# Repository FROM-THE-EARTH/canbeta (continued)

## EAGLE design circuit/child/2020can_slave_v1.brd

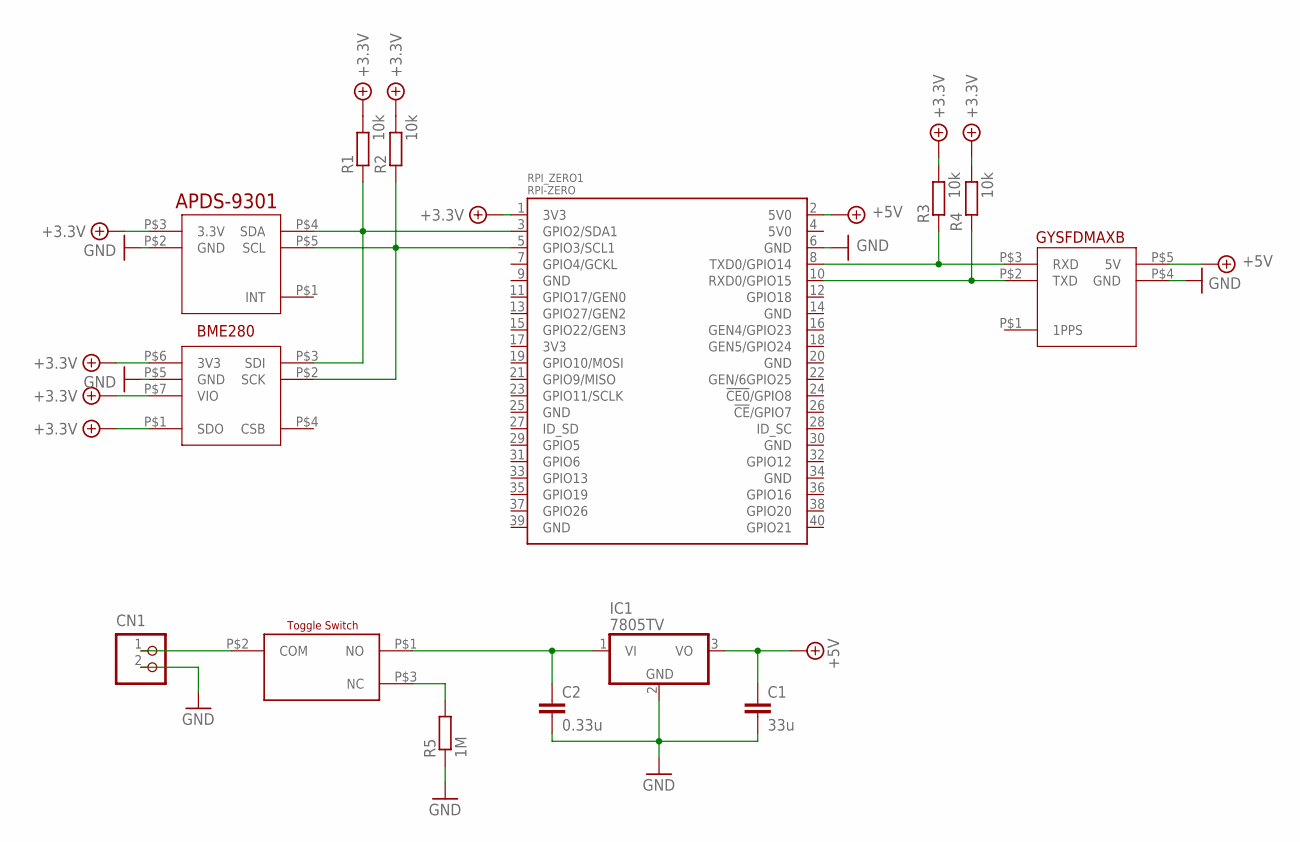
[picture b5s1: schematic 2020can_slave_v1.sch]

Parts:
APDS-9301_V1: APDS-9301_V
BME280-1_V1: BME280-1_V
C1: 33u; C5B3
C2: 0.33u; C5B3
CN1: B2P-VH
GYSFDMAXB_V1: GYSFDMAXB_V
IC1: 7805TV; TO220V
R1, R2, R3, R4: 10k; 0207/10
R5: 1M; 0207/10
RPI_ZERO1: RPI-ZERO; RASP_PI_ZERO_BOARD_FULL
SWITCH_2MS1T2B4M2QES1: SWITCH_2MS1T2B4M2QES

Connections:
+4.1V: APDS-9301_V1.P$3 (3.3V), BME280-1_V1.P$6 (3V3), BME280-1_V1.P$7 (VIO), R1.2, R2.2, R3.2, R4.2, RPI_ZERO1.1 (3V3)
+5V: C1.1, GYSFDMAXB_V1.P$5 (5V), IC1.3 (VO), RPI_ZERO1.2 (5V0)
GND: APDS-9301_V1.P$2 (GND), BME280-1_V1.P$5 (GND), C1.2, C2.2, CN1.2, GYSFDMAXB_V1.P$4 (GND), IC1.2 (GND), R5.1, RPI_ZERO1.6 (GND)
unnamed: APDS-9301_V1.P$4 (SDA), BME280-1_V1.P$3 (SDI), R1.1, RPI_ZERO1.3 (GPIO2/SDA1)
unnamed: APDS-9301_V1.P$5 (SCL), BME280-1_V1.P$2 (SCK), R2.1, RPI_ZERO1.5 (GPIO3/SCL1)
unnamed: R5.2, SWITCH_2MS1T2B4M2QES1.P$3 (NC)
unnamed: GYSFDMAXB_V1.P$3 (RXD), R3.1, RPI_ZERO1.8 (TXD0/GPIO14)
unnamed: GYSFDMAXB_V1.P$2 (TXD), R4.1, RPI_ZERO1.10 (RXD0/GPIO15)
V+: CN1.1, SWITCH_2MS1T2B4M2QES1.P$2 (COM)
VIN: C2.1, IC1.1 (VI), SWITCH_2MS1T2B4M2QES1.P$1 (NO)

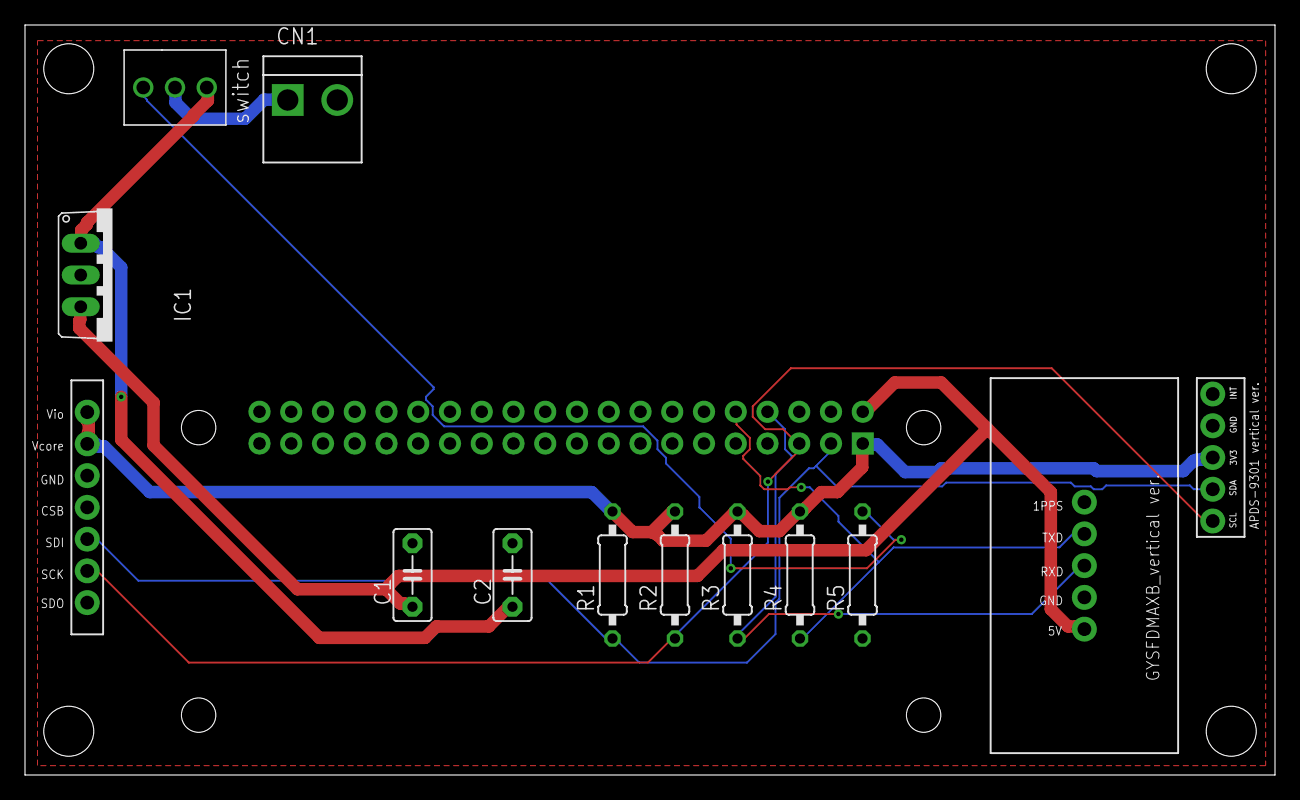
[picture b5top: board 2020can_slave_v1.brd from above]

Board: 2 copper layers, 100.0 x 60.0 mm, 14 parts (1 on the bottom side), 10 nets.

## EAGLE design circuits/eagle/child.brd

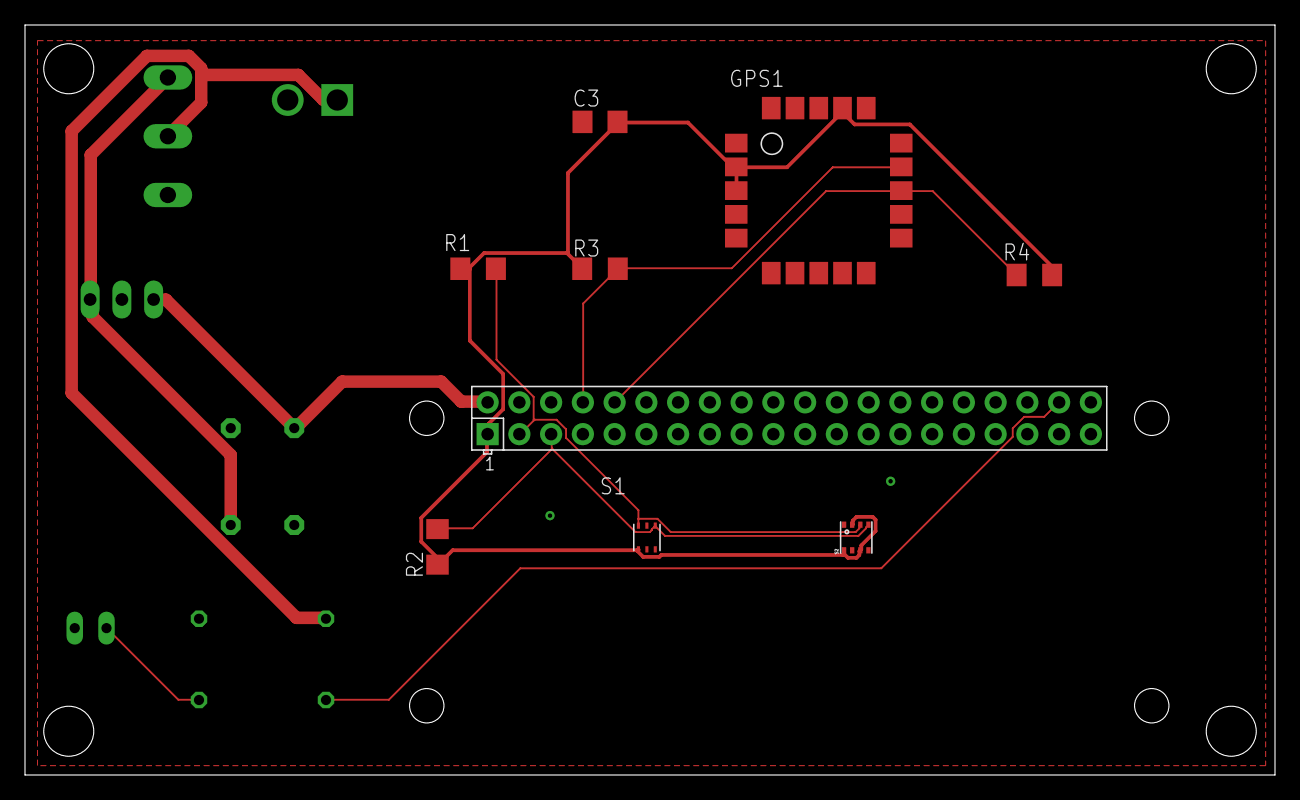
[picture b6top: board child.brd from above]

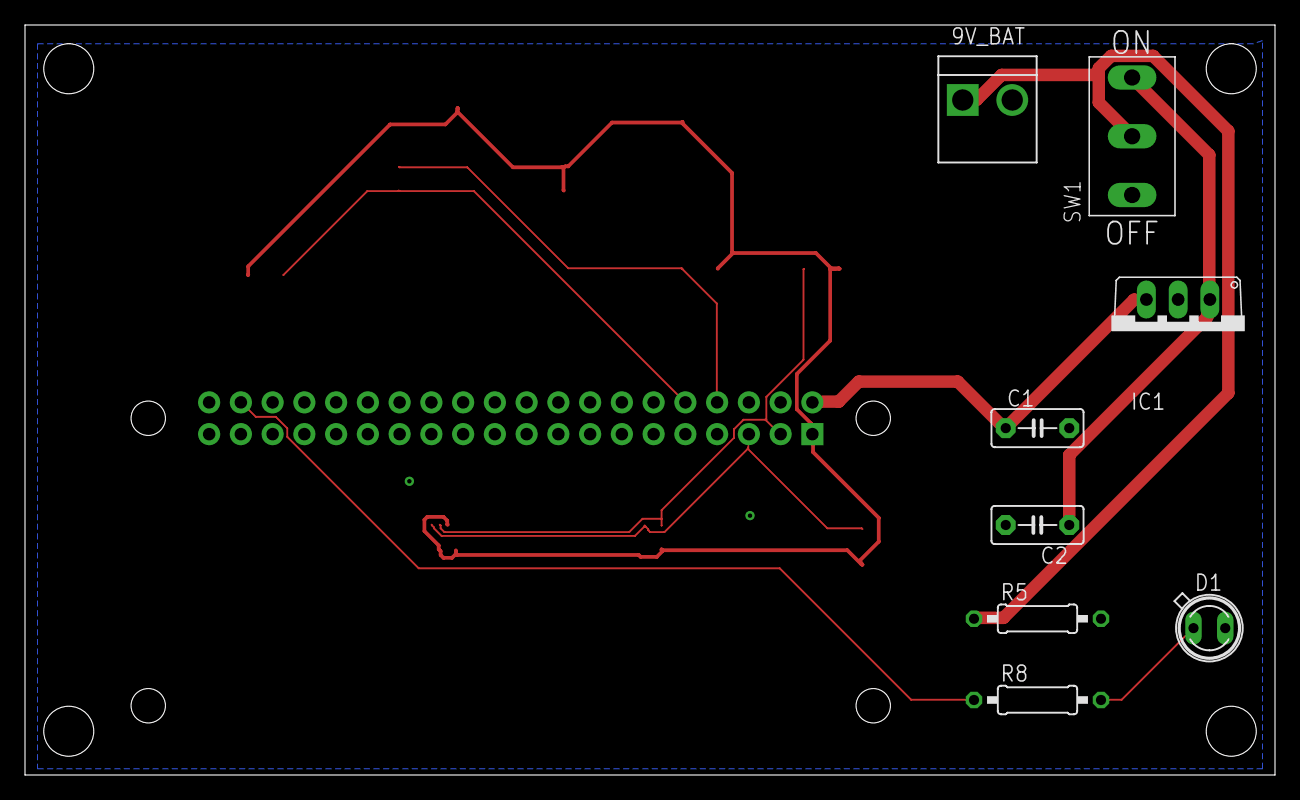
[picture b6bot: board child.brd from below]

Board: 2 copper layers, 100.0 x 60.0 mm, 17 parts (8 on the bottom side), 11 nets.

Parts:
9V_BAT: B2P-VH
C1: 33u; C5B3
C2: 0.33u; C5B3
C3: 0.1u; C1206
D1: SFH482
GPS1: SAM-M8Q
IC1: 7805TV; TO220V
R1, R2, R3, R4: 10k; R1206
R5: 1M; 0207/10
R8: 470; 0207/10
RPI_ZERO1: RPI-ZERO; RASP_PI_ZERO_BOARD_FULL
S1: OPT3002
S2: BME280
SW1: TOGGLE; TOGGLE_1MS1-T1-B1-M2-Q-N-S

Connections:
+3V3: C3.2, GPS1.P$2, GPS1.P$3, GPS1.P$17, R1.2, R2.2, R3.1, R4.1, RPI_ZERO1.1, S1.P$1, S2.P$2, S2.P$6, S2.P$8
+5V: C1.1, IC1.3, RPI_ZERO1.2
GND: 9V_BAT.2, C1.2, C2.2, C3.1, D1.K, GPS1.P$1, GPS1.P$4, GPS1.P$5, GPS1.P$6, GPS1.P$10, GPS1.P$11, GPS1.P$15, GPS1.P$16, GPS1.P$20, IC1.2, R5.2, RPI_ZERO1.9, S1.P$2, S1.P$3, S2.P$1, S2.P$5, S2.P$7
GPS_RXD: GPS1.P$14, R3.2, RPI_ZERO1.8
GPS_TXD: GPS1.P$13, R4.2, RPI_ZERO1.10
unnamed: R8.1, RPI_ZERO1.38
unnamed: D1.A, R8.2
SCL: R2.1, RPI_ZERO1.5, S1.P$4, S2.P$4
SDA: R1.1, RPI_ZERO1.3, S1.P$6, S2.P$3
V+: 9V_BAT.1, R5.1, SW1.P$2
VIN: C2.1, IC1.1, SW1.P$3

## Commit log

2020-08-26 add gitignore
2020-08-26 created node templates
2020-08-26 created main script
2020-08-26 update dependancy for dev-env
2020-08-26 Update LICENSE
2020-08-26 formatted code
2020-08-26 add empty test flies
2020-08-27 modified package to reflect change of pisat
2020-08-28 update to reflect changes of pisat
2020-08-28 add pigpio
2020-08-29 add analysis of the result of Precursor
2020-08-29 add packages for dev
2020-08-29 fix typo
2020-08-29 add legend and fix the unit of gyro
2020-09-10 add hogehoge
2020-09-28 added HogeHoge
2020-09-28 added another hogehoge
2020-09-28 fallin'
2020-09-28 fallin''
2020-09-28 add deque
2020-09-30 add docs to share information about development
2020-09-30 create a script for adding the can09 package into site-packages
2020-09-30 add docs about hardware and testing
2020-10-03 fixed
2020-10-03 added some constants
2020-10-03 add ave calc
2020-10-03 fix misspelled
2020-10-03 fix dependancy of pisat
2020-10-03 add .venv
2020-10-03 add nodes dir in docs
2020-10-04 added some const
2020-10-19 set fethandler in main and para
2020-10-22 add datasheets of devices to be used
2020-10-22 add circuit's data
2020-10-23 add files for flowcharts
2020-10-23 add empty test scripts
2020-10-23 added the flow charts
2020-10-23 added flowchart
2020-10-24 observe gap of acc_x
2020-10-24 add server package for handling wireless commands
2020-10-24 add dir for experiments
2020-10-24 remove SC SIGNAL from the format
2020-10-24 separated RequestParams from Request
2020-10-25 fixed import error and added RequestCommand to represent an exception about command
2020-10-25 added docs for server
2020-10-27 retake
2020-10-27 para&fallin flowchart
2020-10-27 rework falling_node
2020-10-27 update hardware settings
2020-10-29 E2E exp for first phase
2020-10-29 exp_falling
2020-10-29 rm miss files
2020-11-05 removed useless file
2020-11-05 put together flowcharts into a single file
2020-11-05 modified all flowcharts
2020-11-05 added a dir for e2e test
2020-11-05 updated the falling experiment
2020-11-07 added util file
2020-11-10 updated some constants
2020-11-10 deleted some lines
2020-11-10 updated i controller n deleted reset() method
2020-11-12 added sample-timer
2020-11-12 added sample conter
2020-11-13 copied first_running_node.py
2020-11-13 added TODO
2020-11-13 modified some constants
2020-11-14 update because of the update of pisate
2020-11-14 changed setting because of the change of pisat
2020-11-14 add new nodes
2020-11-14 add new dir named image
2020-11-14 update gitignore
2020-11-15 changed accordin to the change in PIDController.py
2020-11-15 added options
2020-11-15 changed ACCEPTABLE_MOE to SSE_RATIO
2020-11-15 added limit_sensitivity_method.py
2020-11-17 wrote without using manager
2020-11-19 Created new directory for the control station
2020-11-19 Added a script for checking current altitude on terminal
2020-11-19 Fixed because of the update of pisat
2020-11-19 Removed and fixed some points where bugs may exist
2020-11-19 update method of falling experiment
2020-11-19 change so that FallingModel can emit relative altitude
2020-11-19 Added new test for tegus
2020-11-19 Fixed typo
2020-11-19 remove im920
2020-11-19 Added results of experiment
2020-11-19 Removed some dependencies because installation troubles occured.
2020-11-19 Added document about trouble shooting
2020-11-20 Updated trouble-shooting about IM920
2020-11-20 Updated trouble-shooting about serial communication
2020-11-20 Added device IDs of IM920
2020-11-20 Fixed typos
2020-11-20 Implemented MissionStandbyNode
2020-11-20 Updated each settings
2020-11-20 Fixed so that any encodings can be used
2020-11-20 Added SocketTransceiver as a component
2020-11-20 Updated scripts for control station
2020-11-20 Removed dev-packages
2020-11-20 Changed baudrate of IM920 and GPS
2020-11-20 Configured main.py of child
2020-11-20 Moved setting of altitude on the ground
2020-11-20 Changed start Node as MissionStandbyNode
2020-11-20 Built MissionStandbyNode.
2020-11-20 Built ChildServerNode.
2020-11-20 Added the attribute of length of request
2020-11-20 Configured commands for child
2020-11-20 Added utilities about IM920
2020-11-20 Added result of heating test
2020-11-20 Fixed bug about no argument commands
2020-11-20 Fixed import error which occurs when sending StartCommand
2020-11-20 Debugged MissionStandbyNode
2020-11-20 Debugged the script for sending start signal
2020-11-21 Changed the serial port for IM920 on the control station
2020-11-21 Fixed RunningModel so that errors do not occur if the body doesn't catch signal from satellites
2020-11-21 Added shell script for setup
2021-06-18 Updated the repository.
2021-06-18 Included *.log files.
2021-06-18 Removed legacy files.
2021-06-18 Deployed 25eeed3 with MkDocs version: 1.2.1
2021-06-18 Updated documents.
2021-06-19 :pencil2: Fixed unappropriate URL of the reporitory site.
2021-06-19 :pencil2: Added several files describing about rules on contributing.
